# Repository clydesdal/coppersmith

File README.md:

# Coppersmith

This started out as a bet.  Its beyond ambitious and will most likely never lead anywhere.
I would very much like to get rid of windows, but need a few important programs.  Altium is
one of them.  This is an experiment to see how far I can come up with a vibe coded layout tool.
So far this is extremely rough.  No code was reversed, or systems copied.  This would probably 
work a lot better if it were.  Anyway, basically I can load/save kicad, Altium, pads all in varying
degrees of functionality.  You can somewhat layout traces, export gerbers.  DRC, Schematic capture, 
libraries are all very broken.  

You can read the rest, but its LLM documentation, so some of it doesn't make sense.

Lay out printed circuit boards: place parts, route copper, check the rules,
and write Gerbers. It wears Copperview's clothes and hands its output straight
to it.

    coppersmith                     open the window with the sample board
    coppersmith BOARD.cspcb         open a board
    coppersmith BOARD.cspcb --gerbers DIR   write Gerbers and drill files, no window
    coppersmith BOARD.cspcb --check         print the rule check, no window

`coppersmith --help` lists every option.

## Working on a board

| Tool | Key | What it does |
|---|---|---|
| Select | S | Click to pick, Shift-click to add, drag to move, drag on empty board to box (left→right takes what's inside, right→left anything touched). Grab a track near its end to move just that end. Double-click a track to pick up everything joined to it. Moving keeps 45° work at 45° (see below). |
| Route | W | Click a pad, via or track to start. Routing works like Altium's: see below. |
| Via | V | Click to drop a via; it takes the net of what it lands on. |
| Outline | O | Click the board's corners; click the first corner (or Enter) to close. |
| Pour | P | Click a copper pour's corners on the layer in use; click the first corner (or Enter) to close. It takes the lit-up net, or the net under its first corner, or GND. See below. |
| Place | (click a footprint in the library) | Click to place, R turns, L puts it on the other side, Esc stops. |

### Copper pours and planes

A pour fills its outline with copper on one layer, keeping its clearance from
everything of other nets, from holes and from the board's edge. Pads of its
own net join it solid or by thermal relief (four spokes across a gap round
the pad). Pieces that touch nothing of its net, pieces smaller than a set
area, and necks narrower than a set width are taken out. Pours go down in
their pour order, each later one keeping clear of those before it.

Pours pour again by themselves whenever a change is finished; while a part
is dragged or a route is laid they keep their old shape, and the router and
pushing take no notice of them, as they'll make way afterwards. Pick a pour
by its dashed outline, or click inside it; its card on the right sets the
net, layer, clearances, how pads join, and the rest. Dragging a pour moves it.

A **power plane** is a pour that ticks *Power plane* (and usually *Covers
the whole board*) on an inner layer: it keeps clear of other nets' holes by
its clearance measured from the hole, as Altium's planes do, and keeps every
piece. Planes are written as ordinary positive copper layers.

A **fill** is copper of a fixed shape (an Altium fill or solid region).
Routing treats it like any other copper.

Gerbers write each poured piece as one region, its holes joined to the
outline by cut-ins.

### Moving keeps the corners

On a board laid at 45°, moving things doesn't leave tracks at odd angles:

- Drag one straight track and it slides sideways, keeping its direction.
  Its neighbours keep theirs too, growing or shrinking to meet it; where the
  track ends on a pad or via, a short 45° leg joins it back. Other nets'
  tracks it runs into are pushed aside (and their vias, with Push vias too
  on), cascading and springing back as in routing. It won't come closer than
  the clearance to pads, holes or the edge: it stops as close as it can get,
  and the status bar says why. When you let go, the rule check runs, and if
  it finds anything new too close the slide is taken back.
- Move a part, a via, or a group, and each track joined to it keeps its
  direction while the next corner slides along the following track; a track
  with nowhere to slide is re-laid as a straight leg and a 45° leg.
- Drag the corner where tracks meet and they're re-laid from their far ends
  in 45° legs.
- Pushed tracks keep 45° too.

### Moving pushes

Anything you drag pushes other nets' tracks out of its way, and their vias
with Push vias too on: a part's pads, a via, a slid track, tracks moved
together, a dragged corner or track end. Turning (R) and flipping (L) a part
push too. Pushes cascade, keep 45°, and spring back as you drag back.

Nothing that moves comes within the clearance of what can't be pushed (other
parts' pads, holes, the board edge): the drag stops as close as it can get
and the status bar says why. When you let go, the rule check runs, and if it
finds anything new too close to something you didn't move, the move is taken
back. A part's own tracks tangling with its pads after a turn is left for you
to tidy, and the checks show where. Hold **Ctrl** while
dragging to move freely without pushing; the rule check then just shows
anything that's too close.

Tracks that weren't at a multiple of 45° to begin with just stretch, so
any-angle work stays as it was drawn.

Arc corners stay arcs. Slide a straight track that runs into a rounded
corner and the arc keeps its radius and stays tangent, while the straight
track beyond it grows or shrinks along its own line. Drag an arc itself and
its radius changes, staying tangent to the tracks either side: pull it out
for a bigger radius, in for a smaller one, never tighter than the Shortest
45° rule. Moving a part or via does the same for the tracks joined to it: a
straight track into a rounded corner keeps its direction while the corner
moves along the track beyond, and an arc starting at a pad moves with the
pad while what's beyond it follows, still tangent.

### No square corners

The board rule **Shortest 45°** (0.5 mm unless you change it, in the Rules
card) keeps 45° work from closing up into right angles:

- Routing at 45°, a turn of 90° or more is cut with 45° steps at least that
  long (one for a right angle, two for a sharper turn), and a 45° step that's
  too short is lengthened, wherever the clearance allows. That includes the
  corner at a click point, which may shorten the piece placed before it.
  Where there's no room to cut, the short stretch is re-laid as a straight
  leg and a 45° leg.
- Moving, a square corner a move makes is cut the same way, and a move that
  would squeeze a 45° step below the rule stops there instead.
- Pushed tracks get the same treatment at the corners a push makes.

The 90° and arc corner styles keep their corners: that's what they're for.

### Routing

While routing, the router shows what a click would lay from the route's end
to the pointer. A click places everything except the last, hollow segment
(the look-ahead), so you set where a corner goes without committing to what
comes after it. Landing on a pad, via or track of the same net places the lot
and ends the route.

| Key | While routing |
|---|---|
| Shift+Space | Corners: 45°, 45° with arc, 90°, 90° with arc, any angle |
| , and . | Arc radius down and up a mil (0.0254 mm); with Shift, ten mils |
| Space (or /) | Flip which way the corner goes |
| Shift+R | When something's in the way: walk around it, push it aside, hug and push, stop at it, or ignore it (shows what it would run over, outlined red, but still only places what's clear) |
| Ctrl+click | Finish the connection by itself, round whatever is in the way |
| Ctrl | Hold to stop the pointer snapping to pad centres |
| V | Via, and carry on on the other side |
| 2 | Via here, same layer |
| + − PgUp PgDn | Change layer, dropping a via |
| 1 | Look-ahead segment on or off |
| 3 | Width from: your choice → rule minimum → rule preferred |
| Shift+D | Take out old paths a new route replaces (on by default) |
| Ctrl+W | Shade the clearance round other nets |
| Backspace | Take back the last click |
| Enter | Same as a click |
| Esc, right-click, double-click | End the route, keeping what's placed |

The same settings are in the routing pill on the toolbar. Walking round is
an A* search on a fine grid kept clear of other nets and the board edge,
then pulled straight wherever an exact clearance check allows.

**Push** goes round what can't move (pads, vias, holes, the board edge) and
through other nets' tracks, which bend out of its way. Each track is bent as
little as it can be, its ends stay where they are, and a pushed track pushes
whatever it then runs into. Move the pointer away and they spring back; a
click keeps them. If a track can't give way (pinned between pads, or it
would have to go the long way round) the route walks round instead and the
routing chip says so. Backspace and Ctrl+Z put pushed tracks back too.

With **Push vias too** on (it is by default), a via in the way moves the
least it can to a spot that's clear of what can't move on every layer, and
its tracks on every layer follow it with a short jog. On the other layers the
moved via and the tracks that followed it push those layers' tracks aside in
turn, layer after layer until everything settles; the route being laid shows
the board as it would be left, every layer included. If another layer can't
make room, the via stays put and the route goes round or pushes otherwise. Only the
stretch of a pushed track near the trouble changes; the rest stays exactly
where it was.

**Hug and push** keeps close round what's in the way while that's a fair
path, and pushes only when going round would be the long way or no way.

**Arc corners** plan the route with sharp corners, then round each into a
tangent arc of the arc radius (shown in the routing chip). A corner's arc can
use up to half of each segment it shares with another corner. An arc that
would come too close to something tries half the radius, and so on, or the
corner stays sharp. Arcs are real arcs on the board and in the Gerbers
(G02/G03); moving their ends keeps their shape. Arcs are pushed like any
other track: a run with arc corners is bent as if each arc were the corner it
rounds off, then its corners are rounded again — the old ones at their old
radii, new ones at the run's, each shrinking if it would come too close.

**The clearance always holds.** Every mode plans clear paths, and before
anything is placed (a route, a pushed track, a moved via, a dropped via)
the rule check is run on the result: if it would call anything too close,
shorted or too near the edge, nothing is placed and the status bar says why.

While dragging a part, **Space** turns it 90° (Shift+Space the other way),
as do R and Shift+R, and L puts it on the other side; the drag carries on
with it turned. Space and R turn a part you're placing from the library too.

Anywhere: R turn 90° (Shift+R the other way), L other side, Delete remove,
Ctrl+D copy, Ctrl+A everything, N light up the net under the pointer, 1–6 or
+/− or PgUp/PgDn change copper layer, F fit, X see it from underneath,
G grid, U units, Ctrl+Z / Ctrl+Shift+Z undo and redo, Ctrl+S save (⌘ on a Mac for all the Ctrl keys),
Ctrl+O open, Ctrl+N new, Ctrl+E write Gerbers. Scroll or pinch to zoom,
right- or middle-drag to pan.

The rule check runs all the time: problems are marked on the board and listed
on the right; click one to go to it.

## Files

Boards are saved as `.cspcb`, which is plain JSON (millimetres, Y up). An
arc track has a `mid` point on the way from `a` to `b`, as KiCad does. Parts on
a board carry a copy of their footprint, so a board file stands on its own.

Gerbers are RS-274X with X2 attributes and Altium's file endings (GTL, GBL,
G1…, GTS, GBS, GTP, GBP, GTO, GBO, GKO) plus `-PTH.drl` and `-NPTH.drl`
Excellon files, which every board maker and Copperview read. After writing
them, **View in Copperview** opens them there.

## Footprints

The common packages are built in, made from their datasheet sizes: chip
resistors, capacitors and LEDs (0402–1206), SOIC, TSSOP, QFN, DIP, SOT-23,
SOD-123, TO-220, pin headers, screw terminals, a tactile switch, a 3225
crystal, mounting holes and a test pad.

Your own go in a `footprints` folder in Coppersmith's data folder (the folder
button above the library opens it):

| | |
|---|---|
| Linux | `~/.local/share/coppersmith/footprints/` |
| macOS | `~/Library/Application Support/coppersmith/footprints/` |
| Windows | `%APPDATA%\coppersmith\footprints\` |

Put one footprint or a list per file, in the
same shape as a footprint in a board file. A file can replace a built-in
footprint by using its name.

### Altium and Circuit Studio libraries

Coppersmith reads Altium Designer and Circuit Studio libraries: `.PcbLib`
footprints, `.SchLib` symbols, and `.IntLib` integrated libraries (which hold
both). Add one with the **+** button above the footprint list: it's copied
into your footprint folder and its footprints appear under the library's
name, ready to place. A footprint takes its name letter (R, C, U…) from the
symbol that uses it, when the library has symbols.

Pads (round, oval, rectangular and rounded; through-hole, plated or not),
silkscreen, and courtyard and assembly drawings on mechanical layers come
across. Octagonal pads become rounded rectangles and slotted holes round
ones; copper drawn outside pads (copper tracks, fills, custom pad shapes) is
left out — the library list says how many footprints were approximated,
with the details on hover.

    coppersmith --read-altium LIBRARY.IntLib

lists what's in a library, symbols included (pins, prefix, linked footprint),
and what was left out. Symbols are read now and kept for the schematic
editor still to come. Writing Altium libraries is next.

### Altium and Circuit Studio boards and schematics

**Open** also takes `.PcbDoc` and `.CSPcbDoc` boards. The board comes in
unsaved, as a new Coppersmith board: outline, copper layers, parts (with
their footprints as placed), nets, tracks, arcs and vias, fills and solid copper regions, and the design rules (clearance from the
clearance table, track widths, via sizes, mask and edge clearance).

Pours come in as pours, from their outlines and settings (pour order,
dead copper and small-island removal, neck width), with the clearance the
rules give polygons and the polygon-connect rule's direct or relief joins,
and are poured again here rather than copied, so they stay live. Plane
layers become plane pours: one per split plane, or the whole board for a
plane layer with a net and no splits, with the plane clearance and
plane-connect rules and the layer's pullback from the edge. Hatched pours
are poured solid; pour cutouts, shelved pours and free pads are left out.
The status bar says what was left out. Part names sit at Coppersmith's
usual spot, not where Altium had them.

    coppersmith --read-altium BOARD.CSPcbDoc
    coppersmith --read-altium SHEET.SchDoc
    coppersmith --read-altium PROJECT.PrjPcb

summarises a board (with its rules), a schematic sheet (parts, wires,
labels, ports), or a whole project: every sheet's netlist joined up and
checked net by net against the board, listing any pin the two disagree on.

## Building

Coppersmith is plain Rust (1.88 or newer) and builds the same way on Linux,
macOS and Windows. Get Rust from https://rustup.rs, then:

    cargo build --release        # the program is target/release/coppersmith(.exe)
    cargo test

What each computer needs besides Rust:

| | Needs | Package it |
|---|---|---|
| Linux | a C linker; on Debian/Ubuntu also `libxkbcommon-dev libwayland-dev libgl1-mesa-dev libx11-dev libxcursor-dev libxrandr-dev libxi-dev` | `sh packaging/linux/install.sh` adds it to ~/Applications and the launcher |
| macOS | Xcode command line tools (`xcode-select --install`) | `sh packaging/macos/make-app.sh` makes `target/Coppersmith.app` (`--universal` for Apple Silicon + Intel) |
| Windows | Visual Studio Build Tools, "Desktop development with C++" | `packaging\windows\make-zip.ps1` makes a zip with `coppersmith.exe` |

`.github/workflows/build.yml` builds, tests and packages all three on GitHub.

### Where things are

    src/
      main.rs        command line, opening the window
      pcb/           the board and everything worked out from it — no windows, no OS
        geom.rs        points and the grown-shape sums behind clearance and picking
        model.rs       the board, parts, pads, tracks, vias, nets, rules; the .cspcb file
        library.rs     built-in footprints and your footprint files
        copper.rs      what touches what, and the still-to-connect lines
        pour.rs        pouring copper pours and planes
        drc.rs         the rule check
        router.rs      the interactive router: corner styles, walk round, push, arcs, loops
        slide.rs       moving tracks without losing their 45° corners
        gerber.rs      Gerber and Excellon output
        altium/        reading Altium / Circuit Studio libraries, boards, sheets, projects
        font.rs        the silkscreen stroke font
        sample.rs      the 555 sample board
      ui/            the window
        app.rs         editor state, undo, edits, files, keys
        routing.rs     laying a route: clicks, look-ahead, vias, auto-complete
        view.rs        drawing the board and what the mouse does
        panels.rs      top bar, side panels, status bar
        theme.rs       Copperview's colours and fonts
        icons.rs       line icons, the app picture
        play.rs        scripted input for picture checks
      platform/      what differs between Linux, macOS and Windows
        mod.rs         data folder, opening folders, finding programs, install, console
        pinch_wayland.rs  trackpad pinches on Linux (macOS and Windows get them free)
        install_linux.rs  ~/Applications and the launcher entry
    assets/          fonts (built in, so it looks the same everywhere) and icons
    packaging/       per-platform install and bundle scripts

Anything that touches the operating system goes in `platform/`, so `pcb/`
and `ui/` stay the same on every computer.

### Checking by picture

    coppersmith --screenshot out.png --zoom 25,18,30 --play 'key w; bclick 27.475 16.095; bclick 29 9.0875'

`--play` acts out mouse and key steps; `bclick X Y` and friends take board
millimetres, so scripts keep working whatever size the window is. Plain
`click X Y` takes window points (screenshot pixels divided by the display
scale). `hold ctrl` … `release` holds a key across clicks.

Figtree and JetBrains Mono are included under the SIL Open Font License
(see assets/fonts/OFL.txt and assets/fonts/OFL-JetBrainsMono.txt).

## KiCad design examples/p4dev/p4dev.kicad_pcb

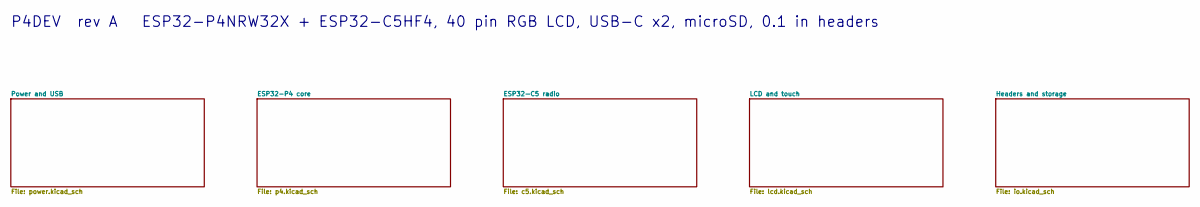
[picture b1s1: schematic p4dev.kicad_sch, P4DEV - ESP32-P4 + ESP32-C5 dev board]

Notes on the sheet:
P4DEV rev A ESP32-P4NRW32X + ESP32-C5HF4, 40 pin RGB LCD, USB-C x2, microSD, 0.1 in headers

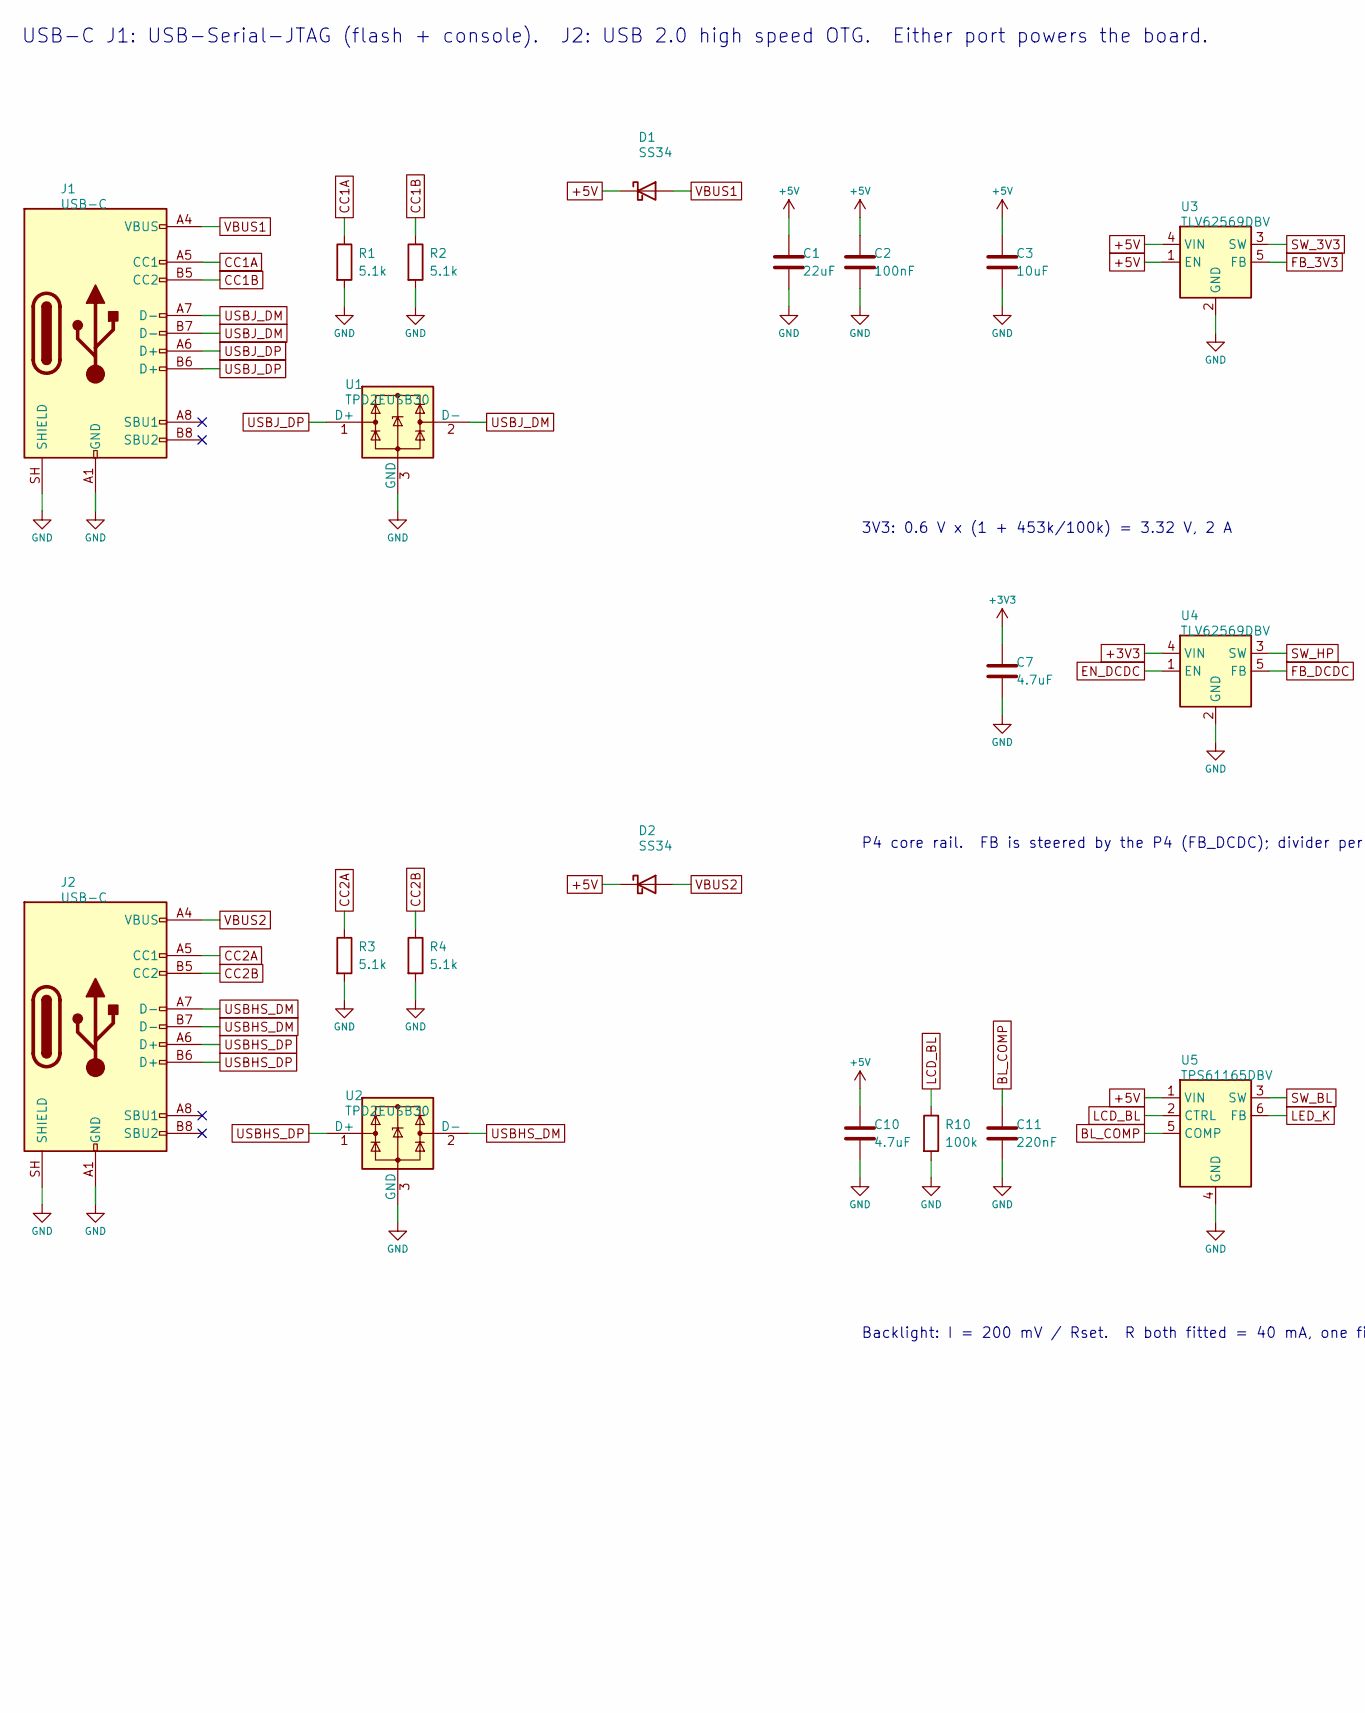
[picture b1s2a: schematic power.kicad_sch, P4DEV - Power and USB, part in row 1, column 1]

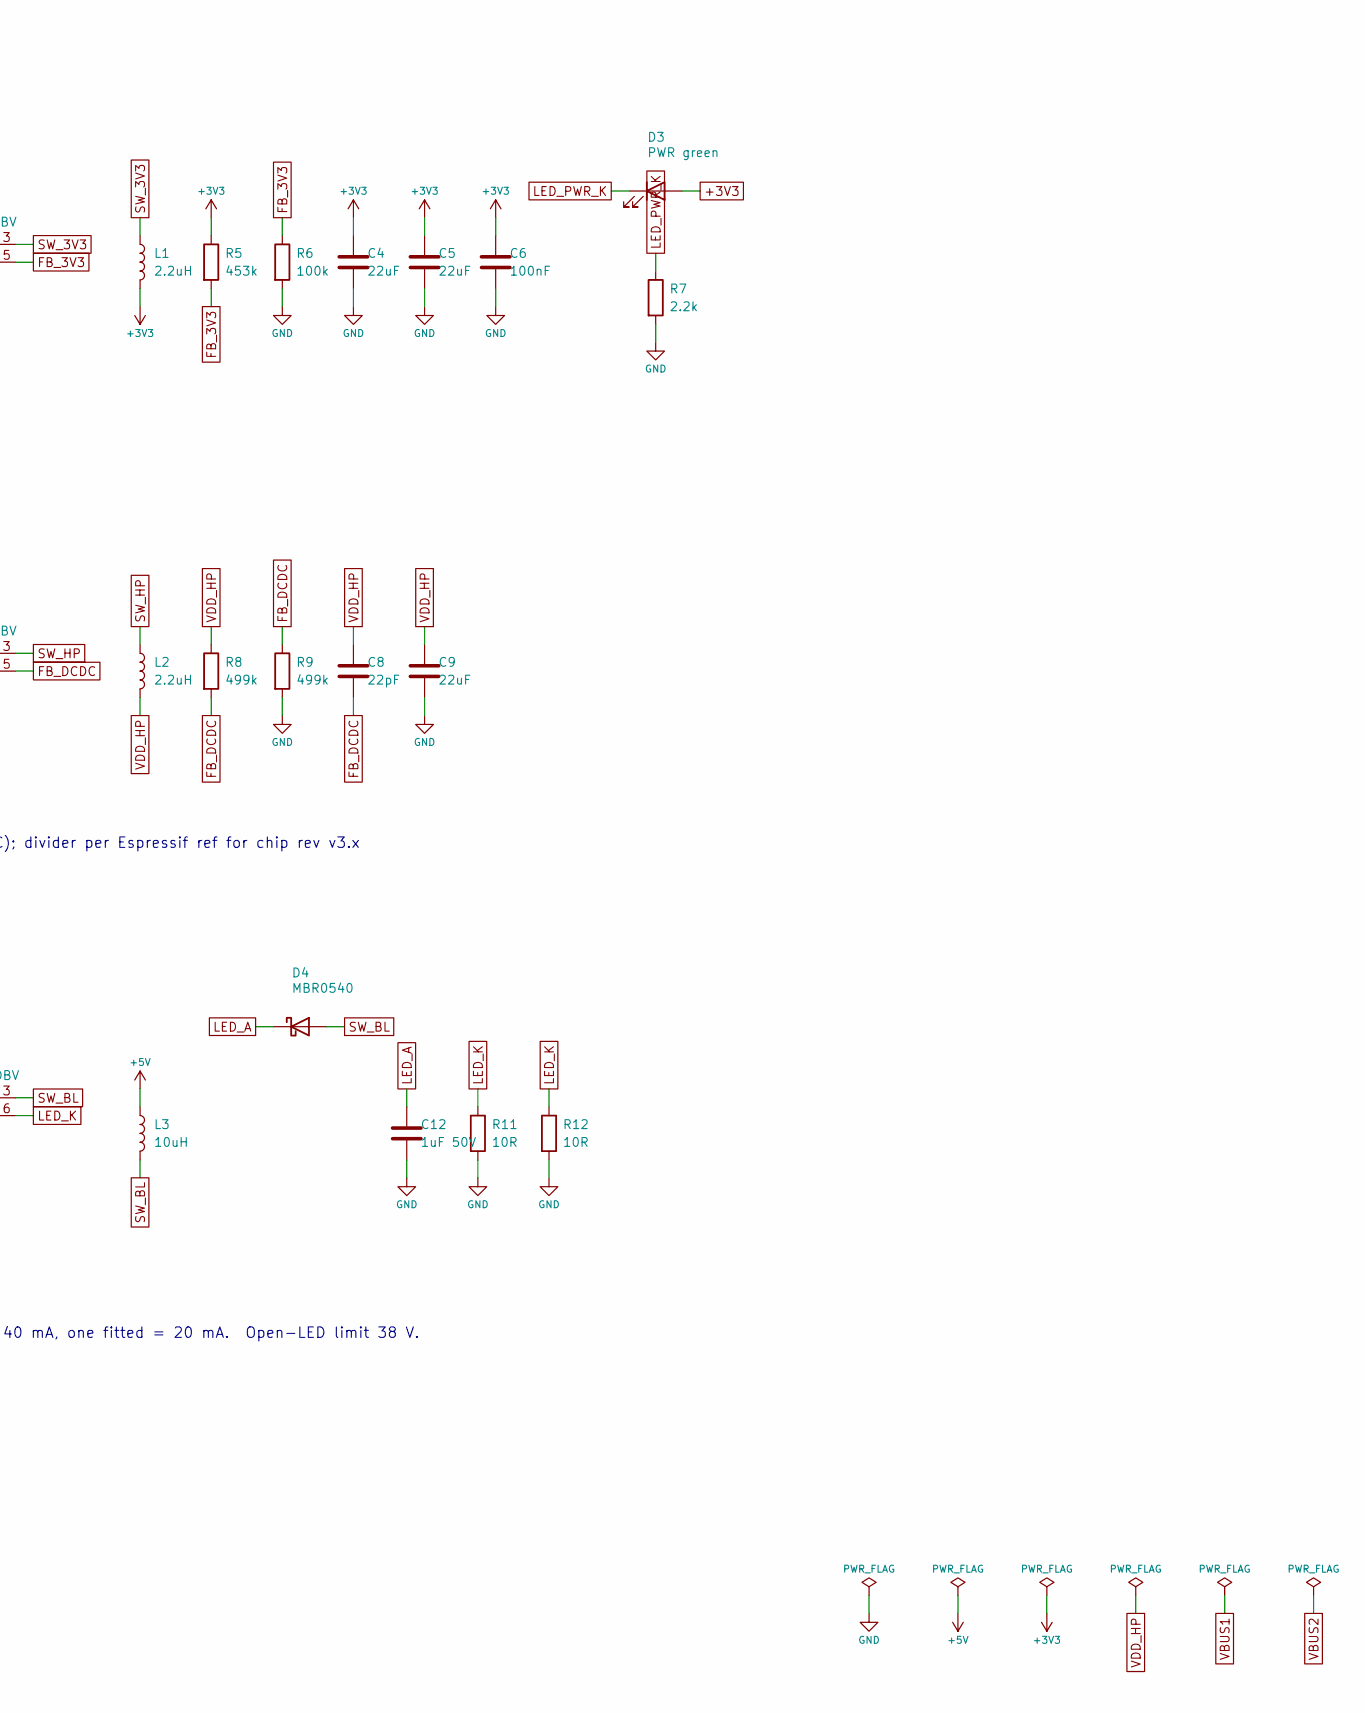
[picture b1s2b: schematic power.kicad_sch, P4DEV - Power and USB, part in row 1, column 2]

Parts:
C1, C4, C5, C9: 22uF; C_0805_2012Metric
C2, C6: 100nF; C_0402_1005Metric
C3: 10uF; C_0603_1608Metric
C7, C10: 4.7uF; C_0603_1608Metric
C8: 22pF; C_0402_1005Metric
C11: 220nF; C_0402_1005Metric
C12: 1uF 50V; C_0805_2012Metric
D1, D2: SS34; D_SMA; MPN SS34
D3: PWR green; LED_0603_1608Metric
D4: MBR0540; D_SOD-123; MPN MBR0540T1G
J1, J2: USB-C; USB_C_Receptacle_HRO_TYPE-C-31-M-12; MPN HRO TYPE-C-31-M-12
L1, L2: 2.2uH; L_Changjiang_FNR4020S; MPN FNR4020S2R2MT
L3: 10uH; L_Changjiang_FNR4020S; MPN FNR4020S100MT
R1, R2, R3, R4: 5.1k; R_0402_1005Metric
R5: 453k; R_0402_1005Metric
R6, R10: 100k; R_0402_1005Metric
R7: 2.2k; R_0402_1005Metric
R8, R9: 499k; R_0402_1005Metric
R11, R12: 10R; R_0603_1608Metric
U1, U2: TPD2EUSB30; Texas_DRT-3; MPN TPD2EUSB30DRTR
U3, U4: TLV62569DBV; SOT-23-5; MPN TLV62569DBVR
U5: TPS61165DBV; SOT-23-6; MPN TPS61165DBVR

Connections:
+3V3: C4.1, C5.1, C6.1, C7.1, D3.2 (A), L1.2, R5.1, U4.4 (VIN); also elsewhere on the board
+5V: C1.1, C2.1, C3.1, C10.1, D1.1 (K), D2.1 (K), L3.1, U3.1 (EN), U3.4 (VIN), U5.1 (VIN); also elsewhere on the board
BL_COMP: C11.1, U5.5 (COMP)
CC1A: J1.A5 (CC1), R1.1
CC1B: J1.B5 (CC2), R2.1
CC2A: J2.A5 (CC1), R3.1
CC2B: J2.B5 (CC2), R4.1
EN_DCDC: U4.1 (EN); also elsewhere on the board
FB_3V3: R5.2, R6.1, U3.5 (FB)
FB_DCDC: C8.2, R8.2, R9.1, U4.5 (FB); also elsewhere on the board
GND: C1.2, C2.2, C3.2, C4.2, C5.2, C6.2, C7.2, C9.2, C10.2, C11.2, C12.2, J1.A1 (GND), J1.A12 (GND), J1.B1 (GND), J1.B12 (GND), J1.SH (SHIELD), J2.A1 (GND), J2.A12 (GND), J2.B1 (GND), J2.B12 (GND), J2.SH (SHIELD), R1.2, R2.2, R3.2, R4.2, R6.2, R7.2, R9.2, R10.2, R11.2, R12.2, U1.3 (GND), U2.3 (GND), U3.2 (GND), U4.2 (GND), U5.4 (GND); also elsewhere on the board
LCD_BL: R10.1, U5.2 (CTRL); also elsewhere on the board
LED_A: C12.1, D4.1 (K); also elsewhere on the board
LED_K: R11.1, R12.1, U5.6 (FB); also elsewhere on the board
LED_PWR_K: D3.1 (K), R7.1
SW_3V3: L1.1, U3.3 (SW)
SW_BL: D4.2 (A), L3.2, U5.3 (SW)
SW_HP: L2.1, U4.3 (SW)
USBHS_DM: J2.A7 (D-), J2.B7 (D-), U2.2 (D-); also elsewhere on the board
USBHS_DP: J2.A6 (D+), J2.B6 (D+), U2.1 (D+); also elsewhere on the board
USBJ_DM: J1.A7 (D-), J1.B7 (D-), U1.2 (D-); also elsewhere on the board
USBJ_DP: J1.A6 (D+), J1.B6 (D+), U1.1 (D+); also elsewhere on the board
VBUS1: D1.2 (A), J1.A4 (VBUS), J1.A9 (VBUS), J1.B4 (VBUS), J1.B9 (VBUS)
VBUS2: D2.2 (A), J2.A4 (VBUS), J2.A9 (VBUS), J2.B4 (VBUS), J2.B9 (VBUS)
VDD_HP: C8.1, C9.1, L2.2, R8.1; also elsewhere on the board

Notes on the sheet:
USB-C J1: USB-Serial-JTAG (flash + console). J2: USB 2.0 high speed OTG. Either port powers the board.
3V3: 0.6 V x (1 + 453k/100k) = 3.32 V, 2 A
P4 core rail. FB is steered by the P4 (FB_DCDC); divider per Espressif ref for chip rev v3.x
Backlight: I = 200 mV / Rset. R both fitted = 40 mA, one fitted = 20 mA. Open-LED limit 38 V.

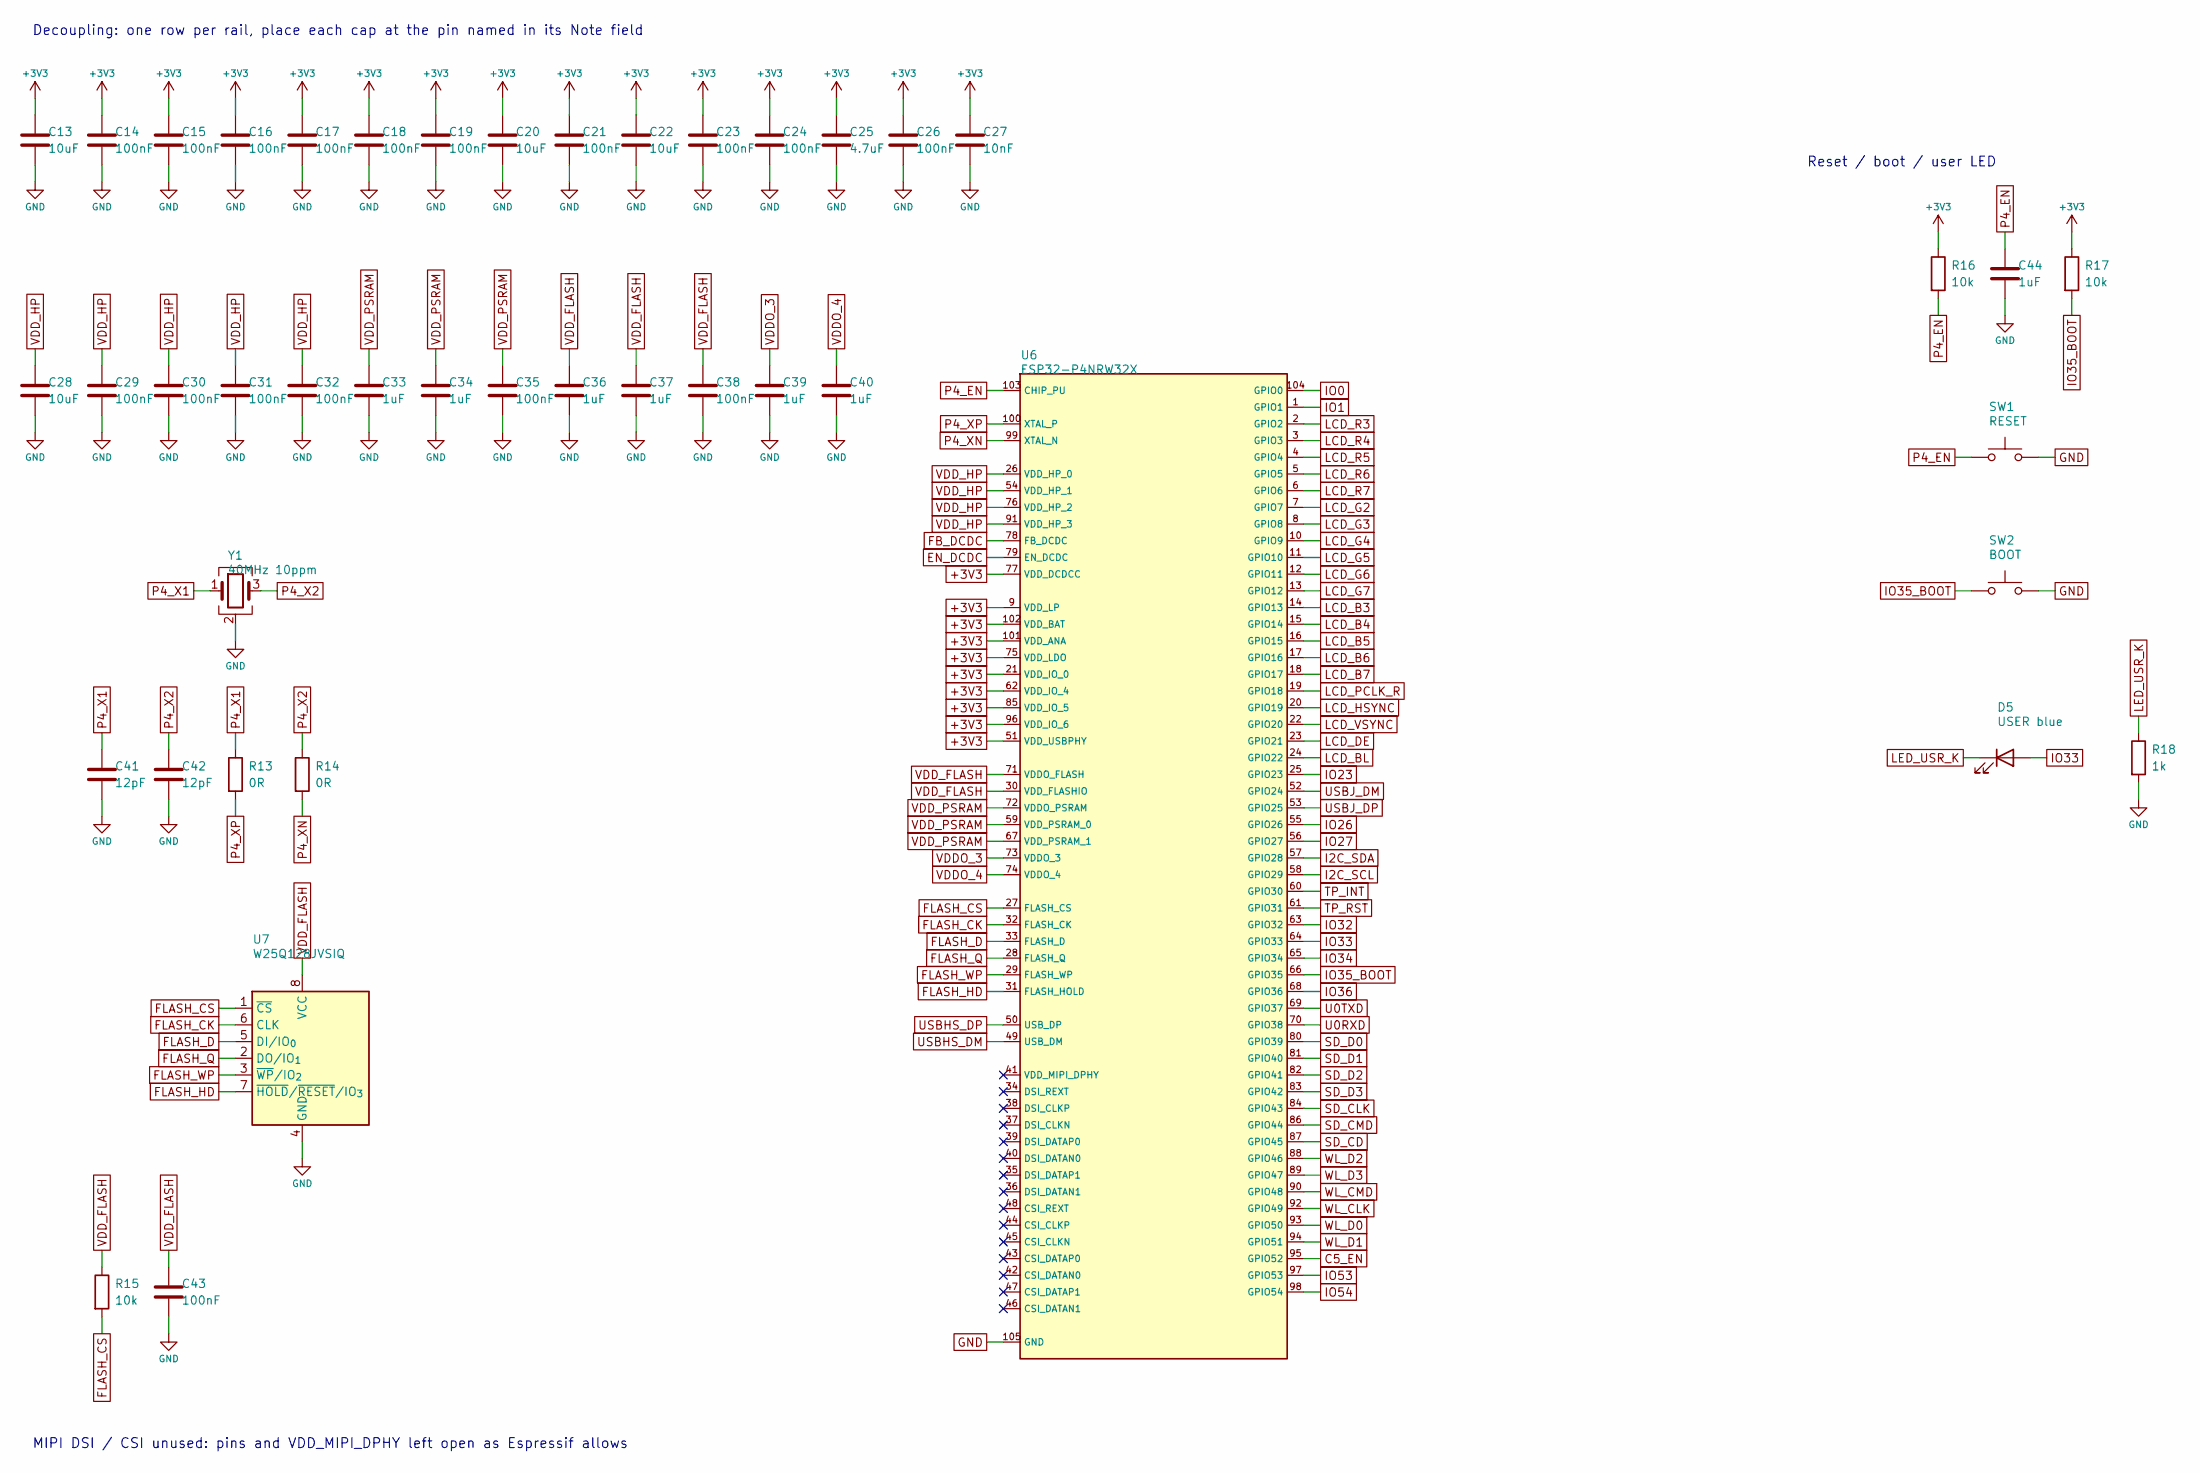
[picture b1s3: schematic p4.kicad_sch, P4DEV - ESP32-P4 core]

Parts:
C13, C20, C22, C28: 10uF; C_0603_1608Metric
C14, C15, C16, C17, C18, C19, C21, C23, C24, C26, C29, C30, C31, C32, C35, C38, C43: 100nF; C_0402_1005Metric
C25: 4.7uF; C_0603_1608Metric
C27: 10nF; C_0402_1005Metric
C33, C34, C36, C37, C39, C40, C44: 1uF; C_0402_1005Metric
C41, C42: 12pF; C_0402_1005Metric
D5: USER blue; LED_0603_1608Metric
R13, R14: 0R; R_0402_1005Metric
R15, R16, R17: 10k; R_0402_1005Metric
R18: 1k; R_0402_1005Metric
SW1: RESET; SW_Push_1P1T_NO_CK_KMR2; MPN C&K KMR221GLFS
SW2: BOOT; SW_Push_1P1T_NO_CK_KMR2; MPN C&K KMR221GLFS
U6: ESP32-P4NRW32X; QFN-104-1EP_10x10mm_P0.35mm_EP7.5x7.5mm; MPN ESP32-P4NRW32X
U7: W25Q128JVSIQ; SOIC-8_5.3x5.3mm_P1.27mm; MPN W25Q128JVSIQ
Y1: 40MHz 10ppm; Crystal_SMD_3225-4Pin_3.2x2.5mm; MPN 40 MHz, CL 10 pF, 3225

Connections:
+3V3: C13.1, C14.1, C15.1, C16.1, C17.1, C18.1, C19.1, C20.1, C21.1, C22.1, C23.1, C24.1, C25.1, C26.1, C27.1, R16.1, R17.1, U6.9 (VDD_LP), U6.21 (VDD_IO_0), U6.51 (VDD_USBPHY), U6.62 (VDD_IO_4), U6.75 (VDD_LDO), U6.77 (VDD_DCDCC), U6.85 (VDD_IO_5), U6.96 (VDD_IO_6), U6.101 (VDD_ANA), U6.102 (VDD_BAT); also elsewhere on the board
C5_EN: U6.95 (GPIO52); also elsewhere on the board
EN_DCDC: U6.79 (EN_DCDC); also elsewhere on the board
FB_DCDC: U6.78 (FB_DCDC); also elsewhere on the board
FLASH_CK: U6.32 (FLASH_CK), U7.6 (CLK)
FLASH_CS: R15.2, U6.27 (FLASH_CS), U7.1 (~CS)
FLASH_D: U6.33 (FLASH_D), U7.5 (DI/IO_{0})
FLASH_HD: U6.31 (FLASH_HOLD), U7.7 (~HOLD/~RESET/IO_{3})
FLASH_Q: U6.28 (FLASH_Q), U7.2 (DO/IO_{1})
FLASH_WP: U6.29 (FLASH_WP), U7.3 (~WP/IO_{2})
GND: C13.2, C14.2, C15.2, C16.2, C17.2, C18.2, C19.2, C20.2, C21.2, C22.2, C23.2, C24.2, C25.2, C26.2, C27.2, C28.2, C29.2, C30.2, C31.2, C32.2, C33.2, C34.2, C35.2, C36.2, C37.2, C38.2, C39.2, C40.2, C41.2, C42.2, C43.2, C44.2, R18.2, SW1.2, SW2.2, U6.105 (GND), U7.4 (GND), Y1.2 (G), Y1.4 (G); also elsewhere on the board
I2C_SCL: U6.58 (GPIO29); also elsewhere on the board
I2C_SDA: U6.57 (GPIO28); also elsewhere on the board
IO0: U6.104 (GPIO0); also elsewhere on the board
IO1: U6.1 (GPIO1); also elsewhere on the board
IO23: U6.25 (GPIO23); also elsewhere on the board
IO26: U6.55 (GPIO26); also elsewhere on the board
IO27: U6.56 (GPIO27); also elsewhere on the board
IO32: U6.63 (GPIO32); also elsewhere on the board
IO33: D5.2 (A), U6.64 (GPIO33); also elsewhere on the board
IO34: U6.65 (GPIO34); also elsewhere on the board
IO35_BOOT: R17.2, SW2.1, U6.66 (GPIO35); also elsewhere on the board
IO36: U6.68 (GPIO36); also elsewhere on the board
IO53: U6.97 (GPIO53); also elsewhere on the board
IO54: U6.98 (GPIO54); also elsewhere on the board
LCD_B3: U6.14 (GPIO13); also elsewhere on the board
LCD_B4: U6.15 (GPIO14); also elsewhere on the board
LCD_B5: U6.16 (GPIO15); also elsewhere on the board
LCD_B6: U6.17 (GPIO16); also elsewhere on the board
LCD_B7: U6.18 (GPIO17); also elsewhere on the board
LCD_BL: U6.24 (GPIO22); also elsewhere on the board
LCD_DE: U6.23 (GPIO21); also elsewhere on the board
LCD_G2: U6.7 (GPIO7); also elsewhere on the board
LCD_G3: U6.8 (GPIO8); also elsewhere on the board
LCD_G4: U6.10 (GPIO9); also elsewhere on the board
LCD_G5: U6.11 (GPIO10); also elsewhere on the board
LCD_G6: U6.12 (GPIO11); also elsewhere on the board
LCD_G7: U6.13 (GPIO12); also elsewhere on the board
LCD_HSYNC: U6.20 (GPIO19); also elsewhere on the board
LCD_PCLK_R: U6.19 (GPIO18); also elsewhere on the board
LCD_R3: U6.2 (GPIO2); also elsewhere on the board
LCD_R4: U6.3 (GPIO3); also elsewhere on the board
LCD_R5: U6.4 (GPIO4); also elsewhere on the board
LCD_R6: U6.5 (GPIO5); also elsewhere on the board
LCD_R7: U6.6 (GPIO6); also elsewhere on the board
LCD_VSYNC: U6.22 (GPIO20); also elsewhere on the board
LED_USR_K: D5.1 (K), R18.1
P4_EN: C44.1, R16.2, SW1.1, U6.103 (CHIP_PU); also elsewhere on the board
P4_X1: C41.1, R13.1, Y1.1
P4_X2: C42.1, R14.1, Y1.3
P4_XN: R14.2, U6.99 (XTAL_N)
P4_XP: R13.2, U6.100 (XTAL_P)
SD_CD: U6.87 (GPIO45); also elsewhere on the board
SD_CLK: U6.84 (GPIO43); also elsewhere on the board
SD_CMD: U6.86 (GPIO44); also elsewhere on the board
SD_D0: U6.80 (GPIO39); also elsewhere on the board
SD_D1: U6.81 (GPIO40); also elsewhere on the board
SD_D2: U6.82 (GPIO41); also elsewhere on the board
SD_D3: U6.83 (GPIO42); also elsewhere on the board
TP_INT: U6.60 (GPIO30); also elsewhere on the board
TP_RST: U6.61 (GPIO31); also elsewhere on the board
U0RXD: U6.70 (GPIO38); also elsewhere on the board
U0TXD: U6.69 (GPIO37); also elsewhere on the board
USBHS_DM: U6.49 (USB_DM); also elsewhere on the board
USBHS_DP: U6.50 (USB_DP); also elsewhere on the board
USBJ_DM: U6.52 (GPIO24); also elsewhere on the board
USBJ_DP: U6.53 (GPIO25); also elsewhere on the board
VDDO_3: C39.1, U6.73 (VDDO_3)
VDDO_4: C40.1, U6.74 (VDDO_4); also elsewhere on the board
VDD_FLASH: C36.1, C37.1, C38.1, C43.1, R15.1, U6.30 (VDD_FLASHIO), U6.71 (VDDO_FLASH), U7.8 (VCC)
VDD_HP: C28.1, C29.1, C30.1, C31.1, C32.1, U6.26 (VDD_HP_0), U6.54 (VDD_HP_1), U6.76 (VDD_HP_2), U6.91 (VDD_HP_3); also elsewhere on the board
VDD_PSRAM: C33.1, C34.1, C35.1, U6.59 (VDD_PSRAM_0), U6.67 (VDD_PSRAM_1), U6.72 (VDDO_PSRAM)
WL_CLK: U6.92 (GPIO49); also elsewhere on the board
WL_CMD: U6.90 (GPIO48); also elsewhere on the board
WL_D0: U6.93 (GPIO50); also elsewhere on the board
WL_D1: U6.94 (GPIO51); also elsewhere on the board
WL_D2: U6.88 (GPIO46); also elsewhere on the board
WL_D3: U6.89 (GPIO47); also elsewhere on the board

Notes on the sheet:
Decoupling: one row per rail, place each cap at the pin named in its Note field
Reset / boot / user LED
MIPI DSI / CSI unused: pins and VDD_MIPI_DPHY left open as Espressif allows
